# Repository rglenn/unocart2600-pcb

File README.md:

This repository now lives at https://codeberg.org/rglenn/unocart2600-pcb

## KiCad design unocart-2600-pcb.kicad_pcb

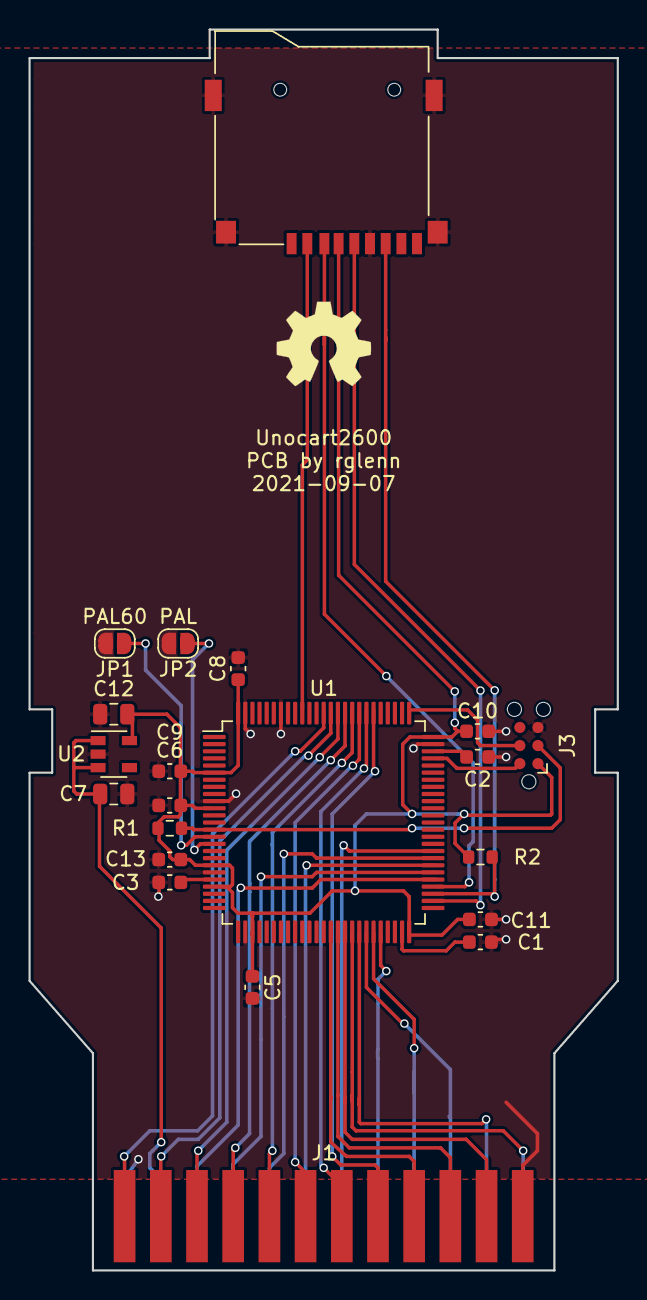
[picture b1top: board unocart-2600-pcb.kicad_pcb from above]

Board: 2 copper layers, 41.3 x 87.1 mm, 21 parts (0 on the bottom side), 36 nets.

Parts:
C1, C2: 2.2u; C_0603_1608Metric
C3, C5, C6, C8, C9, C10, C11, C13: 100n; C_0603_1608Metric
C7, C12: 4.7u; C_0805_2012Metric
J1: Conn_02x12_Counter_Clockwise; 2600-CARTRIDGE
J2: Micro_SD_Card; microSD_HRO_TF_01A
J3: Conn_02x03_Odd_Even; Tag-Connect_TC2030-IDC-NL_2x03_P1.27mm_Vertical
JP1: PAL60; SolderJumper-2_P1.3mm_Open_RoundedPad1.0x1.5mm
JP2: PAL; SolderJumper-2_P1.3mm_Open_RoundedPad1.0x1.5mm
R1, R2: 10K; R_0603_1608Metric
U1: STM32F407VGTx; LQFP-100_14x14mm_P0.5mm
U2: MIC5504-3.3YM5; SOT-23-5

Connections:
+3V3: C5.1, C6.1, C8.1, C9.1, C10.1, C11.1, C12.1, C13.1, J2.4, J3.1, R1.1, R2.2, U1.6, U1.11, U1.19, U1.22, U1.28, U1.50, U1.75, U1.100, U2.5
+5V: C7.1, J1.23, U2.1, U2.3
/A0: J1.8, U1.81
/A1: J1.7, U1.82
/A2: J1.6, U1.83
/A3: J1.5, U1.84
/A4: J1.4, U1.85
/A5: J1.3, U1.86
/A6: J1.2, U1.87
/A7: J1.1, U1.88
/A8: J1.22, U1.55
/A9: J1.21, U1.56
/A10: J1.19, U1.57
/A11: J1.20, U1.58
/A12: J1.18, U1.59
/CS: J2.2, U1.91
/D0: J1.9, U1.39
/D1: J1.10, U1.40
/D2: J1.11, U1.41
/D3: J1.13, U1.42
/D4: J1.14, U1.43
/D5: J1.15, U1.44
/D6: J1.16, U1.45
/D7: J1.17, U1.46
/DI: J2.3, U1.54
/DO: J2.7, R2.1, U1.53
/PAL: JP2.1, U1.16
/PAL60: JP1.1, U1.15
/SCK: J2.5, U1.52
/SWCLK: J3.4, U1.76
/SWDIO: J3.2, U1.72
/~RST: J3.3, R1.2, U1.14
GND: C1.2, C2.2, C3.2, C5.2, C6.2, C7.2, C8.2, C9.2, C10.2, C11.2, C12.2, C13.2, J1.12, J1.24, J2.6, J2.9, J3.5, JP1.2, JP2.2, U1.10, U1.20, U1.27, U1.74, U1.94, U1.99, U2.2
unnamed: C1.1, U1.49
unnamed: C2.1, U1.73
unnamed: C3.1, U1.21

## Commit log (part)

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2018-10-02 Adding project.
2021-09-08 Updating schematic to latest KiCAD libraries Updating PCB to add pull-up resistor on SD card DO Changing to TF-01A push/push MicroSD card socket Updating PCB size to allow a card removal slot on the 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
2021-09-08 Shortening the PCB by 0.5mm after a test fit of a 1:1 printout in the case
2021-09-09 DRC clean, added license text to schematic and PCB

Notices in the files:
unocart-2600-pcb.kicad_pcb:
Copyright Randy Glenn 2021.
This documentation describes Open Hardware and is licensed under the
CERN OHL v. 1.2.
